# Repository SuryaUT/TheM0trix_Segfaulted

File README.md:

# 🕶️ The M0+rix: Segfaulted

A Matrix-themed multiplayer FPS built entirely on the MSPM0G3507 microcontroller. Featuring low-level graphics rendering via raycasting, joystick control, UART-based multiplayer, and a fully custom 3D-printed enclosure.

---

## Table of Contents

* [🎮 Game Description](#-game-description)
* [🔥 Features](#-features)
* [🚀 Getting Started](#-getting-started)
* [🔩 Parts List](#-parts-list)
* [🎮 Controls](#-controls)
* [🖼️ Screenshots / Demo](#️-screenshots--demo)
* [🛠️ Enclosure](#-enclosure)
* [👥 Authors](#-authors)

---

## 🎮 Game Description

Reality is a pointer… and you just dereferenced NULL.

Welcome to **The M0+rix: Segfaulted**, a handheld first-person shooter where the only way out is through the system’s deepest vulnerabilities. Running on the MSPM0 microcontroller, this game turns embedded systems into battlegrounds, with PVP combat over UART and a retro-style 3D world.

Dodge enemy fire, navigate the simulation, and exploit every loophole in the code—because in this world, even one bad instruction could bring everything crashing down. Are you the debugger or just another broken process?

---

## 🔥 Features:

* ✅ First-person shooter with a Matrix-inspired digital battlefield
* ✅ Real-time PVP over UART – battle your opponent in low-level style
* ✅ Optimized for MSPM0 – embedded gaming meets high-speed action
* ✅ Handheld experience – take the simulation anywhere
* ✅ Segfault or escape? – The system is unstable, and only one player will survive

💾 Flash in. Boot up. Overwrite reality.

---

## 🚀 Getting Started

1.  **Clone this repo**

    ```bash
    git clone https://github.com/SuryaUT/TheM0trix_Segfaulted.git
    ```

2.  **Import into Code Composer Studio** <br>
    Open CCS. Go to **File > Import > Code Composer Studio Projects**. Select the cloned folder. Make sure the target is set to **MSPM0G3507**. Click **Finish**.

3.  **Build and Flash** <br>
    Plug in the LaunchPad. Press the build button. Flash to the board.

---

## 🔩 Parts List

| Ref. | Value | Datasheet | Footprint | Qty |
| :--- | :--- | :--- | :--- | :--- |
| C1 | 1uF | ~ | ECE319K:CP\_Radial\_Tantal200mil | 1 |
| C2 | 4.7uF | ~ | ECE319K:CP\_Radial\_Tantal200mil | 1 |
| C3, C4 | 0.1uF | ~ | ECE319K:C\_Axial\_200mil | 2 |
| D1, D4 | LED | Link 1, Link 2 | ECE319K:LED\_D5.0mm | 2 |
| H1, H2, H3, H4 | – | ~ | ECE319K:MountingHole\_4\_40 | 4 |
| J1 | AudioJack | ~ | ECE319K:Jack\_3.5mm\_CUI\_SJ1-3523N\_Horizontal | 1 |
| J2 | Speaker | ~ | ECE319K:PinHeader\_1x02\_P2.54mm\_Vertical | 1 |
| J3 | UART1 | ~ | ECE319K:PinHeader\_1x03\_P2.54mm\_Vertical | 1 |
| J6 | GND | ~ | ECE319K:Testpoint\_1x02\_P2.54mm | 1 |
| J7 | DACOUT | ~ | ECE319K:Testpoint\_1x02\_P2.54mm | 1 |
| J8 | Joystick | SparkFun | ECE319K:SparkfunJoystick | 1 |
| JP1 | TExaS | ~ | ECE319K:PinHeader\_1x03\_P2.54mm\_Vertical | 1 |
| JP2, JP3, JP4 | Jumper\_3\_Open | ~ | ECE319K:PinHeader\_1x03\_P2.54mm\_Vertical | 3 |
| R1 | 470Ω | Resistors | ECE319K:R\_Axial\_DIN0204\_L3.6mm\_D1.6mm\_P7.62mm\_Horizontal | 1 |
| R4–R8 | 1.5kΩ | Resistors | ECE319K:R\_Axial\_DIN0204\_L3.6mm\_D1.6mm\_P7.62mm\_Horizontal | 5 |
| R9–R11 | 12kΩ | Resistors | ECE319K:R\_Axial\_DIN0204\_L3.6mm\_D1.6mm\_P7.62mm\_Horizontal | 3 |
| R12–R15, R17, R19 | 10kΩ | Resistors | ECE319K:R\_Axial\_DIN0204\_L3.6mm\_D1.6mm\_P7.62mm\_Horizontal | 6 |
| R16 | 20kΩ | Resistors | ECE319K:R\_Axial\_DIN0204\_L3.6mm\_D1.6mm\_P7.62mm\_Horizontal | 1 |
| R18 | 220Ω | Resistors | ECE319K:R\_Axial\_DIN0204\_L3.6mm\_D1.6mm\_P7.62mm\_Horizontal | 1 |
| SW1 | RELOAD | ~ | ECE319K:SW\_PUSH\_6mm | 1 |
| SW2 | LEFT | ~ | ECE319K:SW\_PUSH\_6mm | 1 |
| SW3 | SWAP | ~ | ECE319K:SW\_PUSH\_6mm | 1 |
| SW4 | RIGHT | ~ | ECE319K:SW\_PUSH\_6mm | 1 |
| SW5 | SHOOT | ~ | ECE319K:Side\_Switch | 1 |
| TP1 | 3.3V | ~ | ECE319K:Testpoint\_1x02\_P2.54mm | 1 |
| U2 | LP-MSPM0G3507 | TI Dev Board | ECE319K:ti\_LP\_MSPM0G3507 | 1 |
| U3 | MCP34119P | Datasheet | ECE319K:DIP-8\_W7.62mm\_LongPads | 1 |
| U4 | HiLetGo\_ST7735R | Display | ECE319K:hiletgo\_st7735r | 1 |
| U5 | ULN2003B | ULN2003B | ECE319K:DIP-16\_W7.62mm | 1 |
| U6 | TSOP31438 | TSOP31438 | ECE319K:TSOP31438 | 1 |
| ~ | SD Card | ~ | ~ | 1 |
| ~ | Wire Pack | ~ | ~ | 1 |

*Note: Side\_Switch was a custom footprint made by placing surface mount plates the width of switch legs on the front and back of the PCB, such that a switch could be soldered to face away from the side of the PCB, acting like a trigger.*

📦 Full schematic & PCB design files available in “M0+rixPCBFiles” folder

---

## 🎮 Controls

| Control | Action |
| :--- | :--- |
| Joystick | Move Forward, Backward, Strafe Left and Right |
| Trigger Button | Fire weapon |
| Left Button | Rotate Left |
| Right Button | Rotate Right |
| Top Button | Reload/Respawn |
| Bottom Button | Switch Item |

---

## 🖼️ Screenshots / Demo

Gameplay demo available on YouTube [here](https://www.youtube.com/watch?v=fk33UKtkELA).

---

## 🛠️ Enclosure

* Designed in Fusion 360
* Snap-fit top cover
* Gamepad-style ergonomic shell

---

## 👥 Authors

* Elijah Silguero
* Surya Balaji

Special thanks to Dr. Yerrabali, Dr. Valvano, and Dr. Tiwari at The University of Texas at Austin for their instruction and help with this project!

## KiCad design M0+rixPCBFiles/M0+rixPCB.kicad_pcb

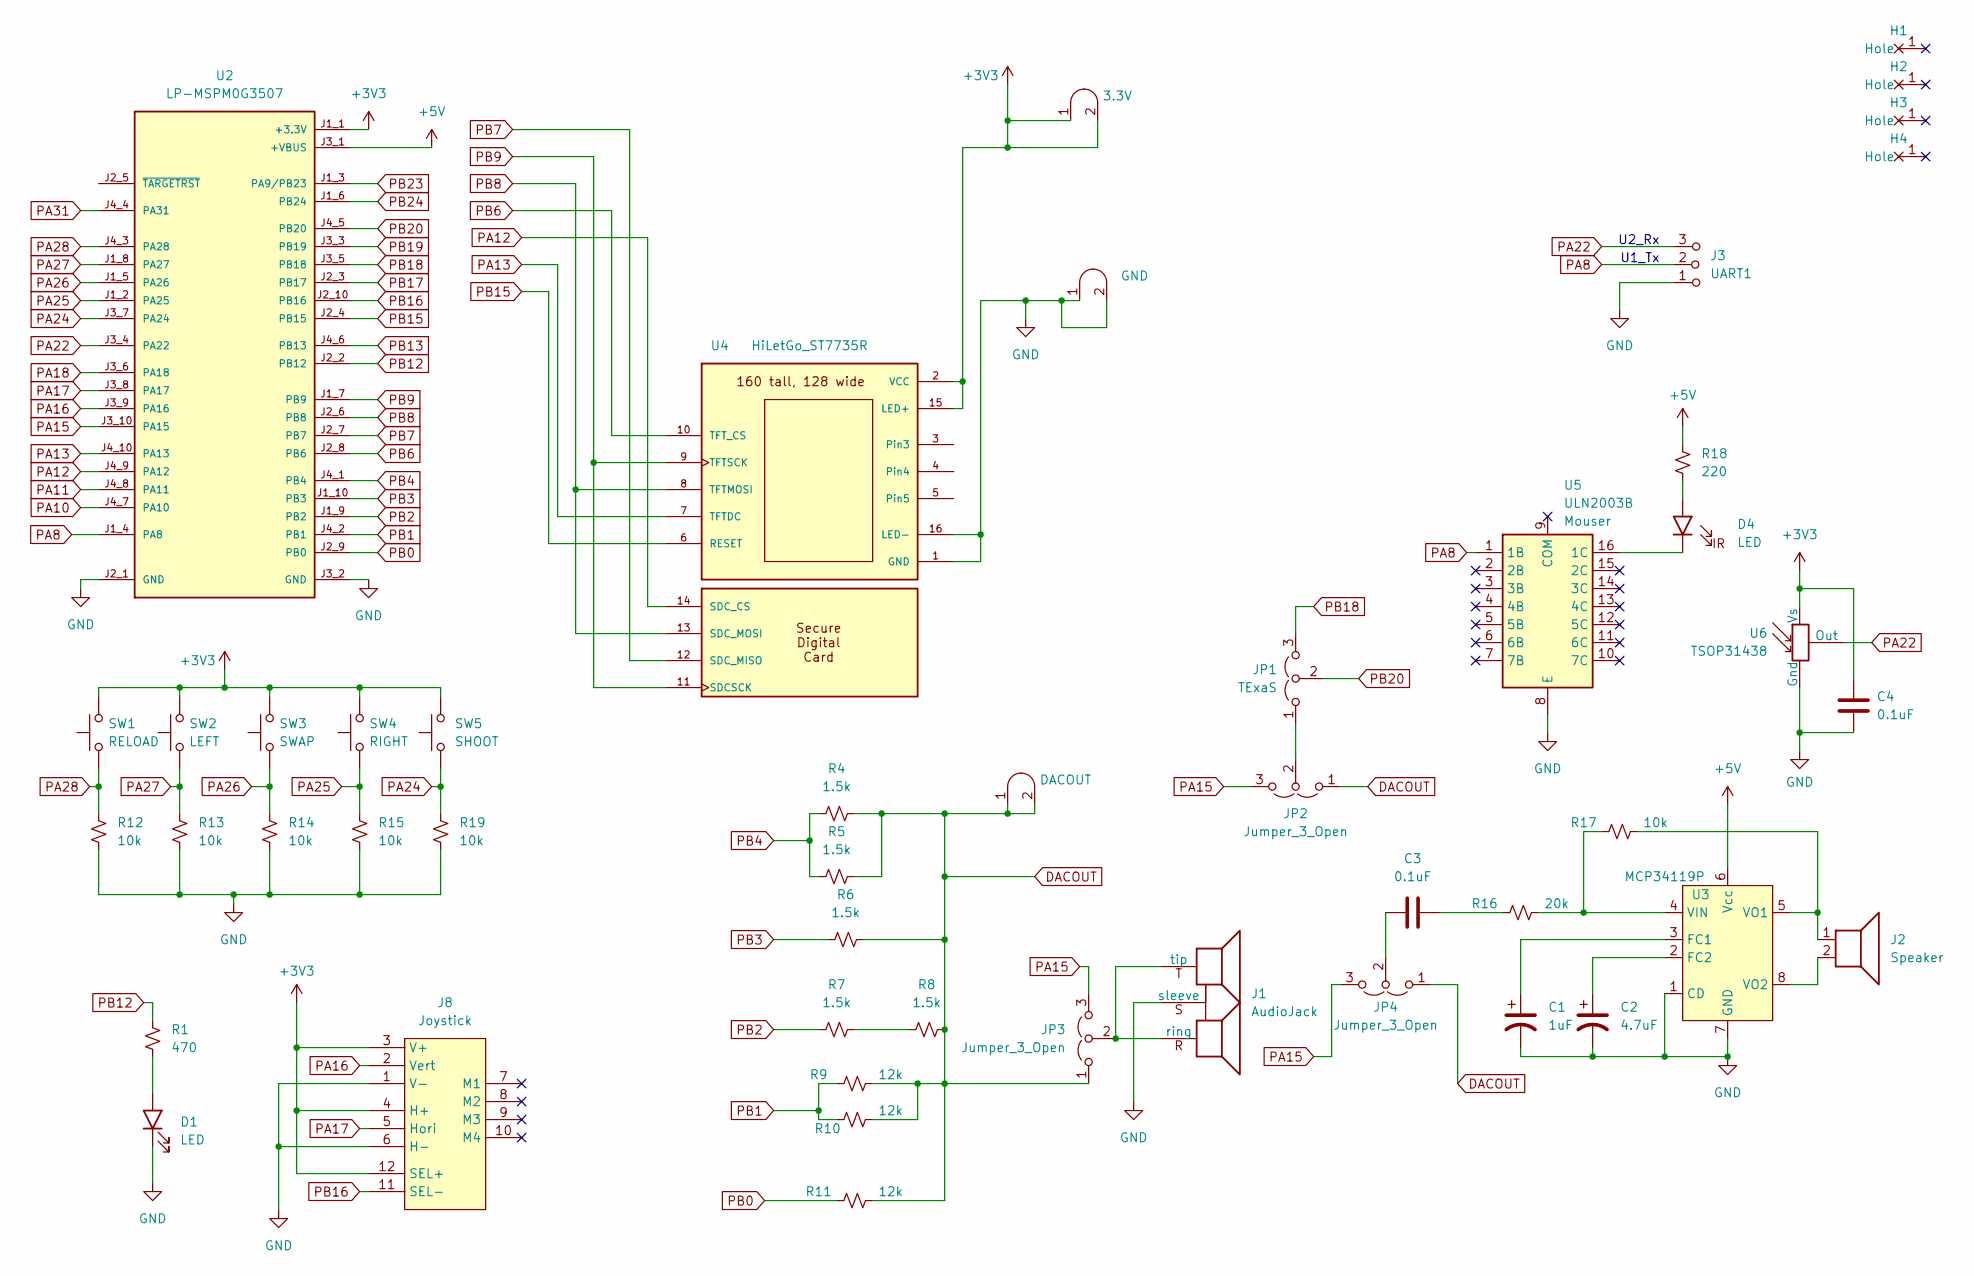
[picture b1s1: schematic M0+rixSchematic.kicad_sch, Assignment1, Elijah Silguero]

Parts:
C1: 1uF; CP_Radial_Tantal200mil
C2: 4.7uF; CP_Radial_Tantal200mil
C3, C4: 0.1uF; C_Axial_200mil
D1, D4: LED; LED_D5.0mm
H1, H2, H3, H4: MountingHole_4_40
J1: AudioJack; Jack_3.5mm_CUI_SJ1-3523N_Horizontal
J2: Speaker; PinHeader_1x02_P2.54mm_Vertical
J3: UART1; PinHeader_1x03_P2.54mm_Vertical
J6: GND; Testpoint_1x02_P2.54mm
J7: DACOUT; Testpoint_1x02_P2.54mm
J8: Joystick; SparkfunJoystick
JP1: TExaS; PinHeader_1x03_P2.54mm_Vertical
JP2, JP3, JP4: Jumper_3_Open; PinHeader_1x03_P2.54mm_Vertical
R1: 470; R_Axial_DIN0204_L3.6mm_D1.6mm_P7.62mm_Horizontal
R4, R5, R6, R7, R8: 1.5k; R_Axial_DIN0204_L3.6mm_D1.6mm_P7.62mm_Horizontal
R9, R10, R11: 12k; R_Axial_DIN0204_L3.6mm_D1.6mm_P7.62mm_Horizontal
R12, R13, R14, R15, R17, R19: 10k; R_Axial_DIN0204_L3.6mm_D1.6mm_P7.62mm_Horizontal
R16: 20k; R_Axial_DIN0204_L3.6mm_D1.6mm_P7.62mm_Horizontal
R18: 220; R_Axial_DIN0204_L3.6mm_D1.6mm_P7.62mm_Horizontal
SW1: RELOAD; SW_PUSH_6mm
SW2: LEFT; SW_PUSH_6mm
SW3: SWAP; SW_PUSH_6mm
SW4: RIGHT; SW_PUSH_6mm
SW5: SHOOT; Side_Switch
TP1: 3.3V; Testpoint_1x02_P2.54mm
U2: LP-MSPM0G3507; ti_LP_MSPM0G3507
U3: MCP34119P; DIP-8_W7.62mm_LongPads
U4: HiLetGo_ST7735R; hiletgo_st7735r
U5: ULN2003B; DIP-16_W7.62mm
U6: TSOP31438

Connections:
+3V3: C4.1, J8.3 (V+), J8.4 (H+), J8.12 (SEL+), SW1.2, SW2.2, SW3.2, SW4.2, SW5.2, TP1.1 (A), TP1.2 (B), U2.J1_1 (+3.3V), U4.2 (VCC), U4.15 (LED+), U6.2 (Vs)
+5V: R18.1, U2.J3_1 (+VBUS), U3.6 (Vcc)
DACOUT: J7.1 (A), J7.2 (B), JP2.1 (A), JP3.1 (A), JP4.1 (A), R4.1, R5.1, R6.1, R8.1, R9.1, R10.1, R11.1
GND: C1.2, C2.2, C4.2, D1.1 (K), J1.S (sleeve), J3.1 (A), J6.1 (A), J6.2 (B), J8.1 (V-), J8.6 (H-), R12.2, R13.2, R14.2, R15.2, R19.2, U2.J2_1 (GND), U2.J3_2 (GND), U3.1 (CD), U3.7 (GND), U4.1 (GND), U4.16 (LED-), U5.8 (E), U6.1 (Gnd)
unnamed: C3.2, R16.2
unnamed: D1.2 (A), R1.2
unnamed: D4.2 (A), R18.2
unnamed: D4.1 (K), U5.16 (1C)
unnamed: J1.R (ring), J1.T (tip), JP3.2 (C)
unnamed: JP1.1 (A), JP2.2 (C)
unnamed: C3.1, JP4.2 (C)
unnamed: R7.1, R8.2
unnamed: C1.1, U3.3 (FC1)
unnamed: C2.1, U3.2 (FC2)
unnamed: R16.1, R17.2, U3.4 (VIN)
unnamed: J2.1, R17.1, U3.5 (VO1)
unnamed: J2.2, U3.8 (VO2)
PA8: J3.2 (B), U2.J1_4 (PA8), U5.1 (1B)
PA10: U2.J4_7 (PA10)
PA11: U2.J4_8 (PA11)
PA12: U2.J4_9 (PA12), U4.14 (SDC_CS)
PA13: U2.J4_10 (PA13), U4.7 (TFTDC)
PA15: JP2.3 (B), JP3.3 (B), JP4.3 (B), U2.J3_10 (PA15)
PA16: J8.2 (Vert), U2.J3_9 (PA16)
PA17: J8.5 (Hori), U2.J3_8 (PA17)
PA18: U2.J3_6 (PA18)
PA22: J3.3 (C), U2.J3_4 (PA22), U6.3 (Out)
PA24: R19.1, SW5.1, U2.J3_7 (PA24)
PA25: R15.1, SW4.1, U2.J1_2 (PA25)
PA26: R14.1, SW3.1, U2.J1_5 (PA26)
PA27: R13.1, SW2.1, U2.J1_8 (PA27)
PA28: R12.1, SW1.1, U2.J4_3 (PA28)
PA31: U2.J4_4 (PA31)
PB0: R11.2, U2.J2_9 (PB0)
PB1: R9.2, R10.2, U2.J4_2 (PB1)
PB2: R7.2, U2.J1_9 (PB2)
PB3: R6.2, U2.J1_10 (PB3)
PB4: R4.2, R5.2, U2.J4_1 (PB4)
PB6: U2.J2_8 (PB6), U4.10 (TFT_CS)
PB7: U2.J2_7 (PB7), U4.12 (SDC_MISO)
PB8: U2.J2_6 (PB8), U4.8 (TFTMOSI), U4.13 (SDC_MOSI)
PB9: U2.J1_7 (PB9), U4.9 (TFTSCK), U4.11 (SDCSCK)
PB12: R1.1, U2.J2_2 (PB12)
PB13: U2.J4_6 (PB13)
PB15: U2.J2_4 (PB15), U4.6 (RESET)
PB16: J8.11 (SEL-), U2.J2_10 (PB16)
PB17: U2.J2_3 (PB17)
PB18: JP1.3 (B), U2.J3_5 (PB18)
PB19: U2.J3_3 (PB19)
PB20: JP1.2 (C), U2.J4_5 (PB20)
PB23: U2.J1_3 (PA9/PB23)
PB24: U2.J1_6 (PB24)

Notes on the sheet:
U2_Rx
U1_Tx

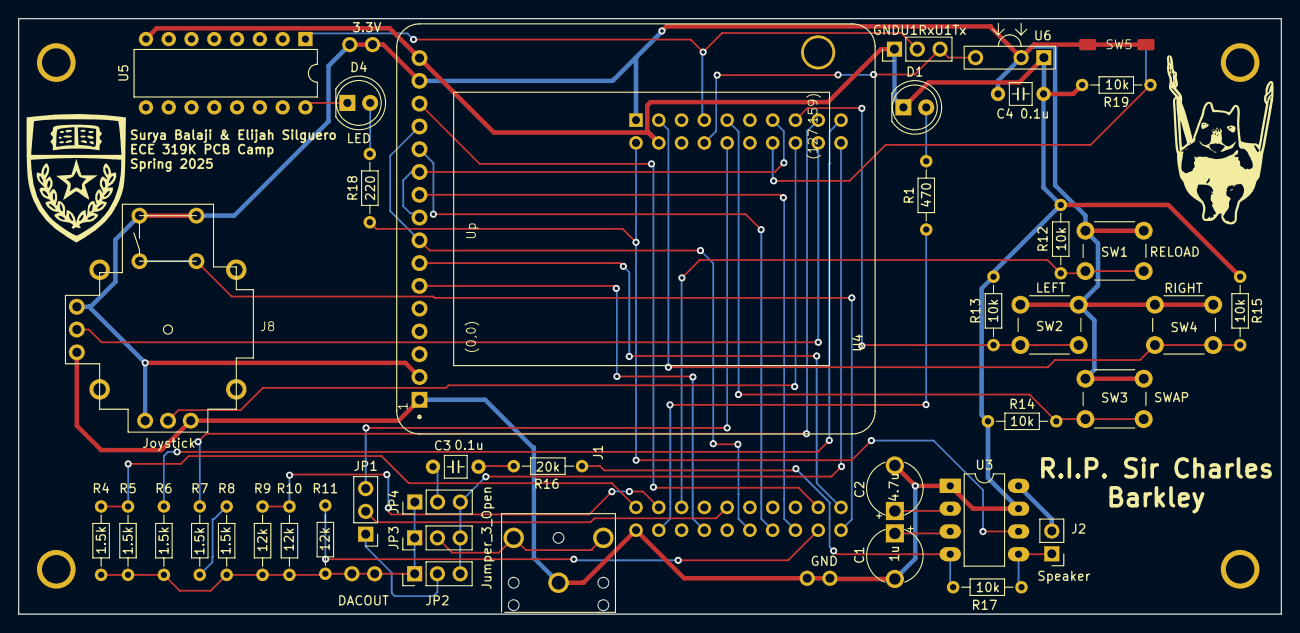
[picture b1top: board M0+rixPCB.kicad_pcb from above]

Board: 2 copper layers, 140.8 x 66.4 mm, 48 parts (1 on the bottom side), 43 nets.

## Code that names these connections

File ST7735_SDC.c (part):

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// **********ST7735 TFT and SDC*******************
// ST7735
// Backlight (pin 10)     to +3.3 V
// MISO (pin 9)           to SPI1 POCI: PB7
// SCK (pin 8)            to SPI1 SCLK: PB9
// MOSI (pin 7)           to SPI1 PICO: PB8
// TFT_CS (pin 6)         to GPIO:  PB6
// CARD_CS (pin 5)        to PA12 (GPIO)
// Data/Command (pin 4)   to PA13 (GPIO), high for data, low for command
// RESET (pin 3)          to PB15 (GPIO)
// VCC (pin 2)            to +3.3 V
// Gnd (pin 1)            to ground

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// ST7735
// LED-   (pin 16) TFT, to ground
// LED+   (pin 15) TFT, to +3.3 V
// SD_CS  (pin 14) SDC, to PA12 chip select
// MOSI   (pin 13) SDC, to PB8 MOSI
// MISO   (pin 12) SDC, to PB7 MISO
// SCK    (pin 11) SDC, to serial clock
// CS     (pin 10) TFT, to PB6  GPIO
// SCL    (pin 9)  TFT, to PB9  SPI1 SCLK
// SDA    (pin 8)  TFT, to PB8  MOSI SPI1 PICO
// A0     (pin 7)  TFT, to PA13 Data/Command, high for data, low for command
// RESET  (pin 6)  TFT, to PB15 reset (GPIO), low to reset
// NC     (pins 3,4,5)
// VCC    (pin 2)       to +3.3 V
// GND    (pin 1)       to ground
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#include <stdio.h>
#include <stdlib.h>
#define SDC_CS_PA12 1
#define TFT_CS_LOW()     (GPIOB->DOUTCLR31_0 = (1<<6))   // PB6 low
#define TFT_CS_HIGH()    (GPIOB->DOUTSET31_0 = (1<<6))   // PB6 high

// PA12 output used for SDC CS
#if SDC_CS_PA12
#define SDC_CS           GPIOA
#define SDC_CS_PIN       (1<<12)         // CS controlled by software
#define SDC_CS_LOW()     (SDC_CS->DOUTCLR31_0 = SDC_CS_PIN)   // PA12 low
#define SDC_CS_HIGH()    (SDC_CS->DOUTSET31_0 = SDC_CS_PIN)   // PA12 high
#endif
// disk_initialize will initialize SPI1 for both TFT and SDC
// 16 rows (0 to 15) and 21 characters (0 to 20)
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void TFT_OutData(char data){char response;
 // while((SPI1->STAT&0x02) == 0x00){}; // spin if TxFifo full
  while((SPI1->STAT&0x10) == 0x10){}; // spin if SPI busy
  SDC_CS_HIGH(); // PA12 high
  TFT_CS_LOW();  // PB6 low
  GPIOA->DOUTSET31_0 = 1<<13;         // RS=PA13=1 for data
  SPI1->TXDATA = data;
  while((SPI1->STAT&0x04) == 0x04){}; // spin SPI RxFifo empty
  response = SPI1->RXDATA; // has no meaning, flush
  TFT_CS_HIGH();  // PB6 high
}
 //---------TFT_OutCommand------------
 // Output 8-bit command to SPI port
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 // Output: none
 void TFT_OutCommand(char command){char response;
   while((SPI1->STAT&0x10) == 0x10){}; // spin if SPI busy
   SDC_CS_HIGH(); // PA12 high
   TFT_CS_LOW();  // PB6 low
   GPIOA->DOUTCLR31_0 = 1<<13;         // RS=PA13=0 for command
   SPI1->TXDATA = command;
   while((SPI1->STAT&0x10) == 0x10){}; // spin if SPI busy
   response = SPI1->RXDATA; // has no meaning, flush
   TFT_CS_HIGH();  // PB6 high
 }
// Companion code to the above tables.  Reads and issues
// a series of LCD commands stored in ROM byte array.
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
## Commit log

2025-03-27 Implimented Textured Walls
    Next Steps: merge with buffer to eliminate smearing and work on bitmap conversion to create detailed custom textures
2025-03-27 Implimented .bmp to texture conversion
    made .py script to convert .bmp files to c arrays for usable textures
2025-03-27 Updared Textures.c for .bmp use
    Tested .bmp converted c arrays in textures with 8 tests (8th successful!!!)
2025-03-27 Added another .bmp texture and updated converter
    made texture 7 a different circuit board texture and updated converter to create const instead of static const arrays
2025-03-27 Generalized converter & added Sir Charles Barkley
    Sir Charles Barkley is in the game as a texture (will be easter egg), and converter has titles of arrays generalized to "myTexture"
2025-03-27 Added more textures and defined texture indicies
    Added two matrix textures to textures.c, defined indices with names for clarity, and cleaned extraneous comments on graphics.c for readability
2025-03-27 Adjusted printed c array format
2025-03-27 Texture index definitions in textures.h
2025-03-27 Implemented textures with buffer
2025-03-28 Updated resolution of textures to 64 x 64
    Rewrote bitmap to C converter Python script for 64 x 64 bitmap conversion, changed definitions in both bitmap to C converter Python script and textures.h to 64 x 64
2025-03-28 Create test
2025-03-28 Uploaded texture bmps and pngs
2025-03-28 Converter takes folder & writes to .txt file
    bmp to C array converter takes folder with both/either png and/or bmp files and writes output to .txt file for easy copying; added new arrays to textures.h; TexArrays.txt is text file to write C arra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
2025-03-28 Added comments of directory to simplify use
2025-03-29 Sprites
2025-03-29 Full upload
2025-03-29 add .gitignore
2025-03-29 Update project name
2025-03-29 test
2025-03-29 Added Foreground Sprites
2025-03-31 Reorganized input functions
2025-03-31 Added new sounds and ammo logic
2025-03-31 began inventory implementation/graphics
2025-04-01 Progress on inventory implementation
2025-04-01 Added shotgun to items
2025-04-02 Added sprint ability from joystick button
2025-04-02 Dynamic ammo for different weapons
2025-04-03 Added gun flash, expiring items, dynamic crosshair
2025-04-03 Added ammo pickup
2025-04-04 Fixed inventory game logic bugs
2025-04-04 Fixed ammo game logic bugs
2025-04-04 Prepare for 2-player by adding otherHealth
2025-04-05 Added sound for realoading with no ammo
2025-04-05 Begin UART
2025-04-05 Fixed muzzle position bug
2025-04-06 UART char transmission
2025-04-06 Implimented cross controller UART position updates
2025-04-07 Synchronized player positions to move enemy sprite
2025-04-07 added interrupt for uart transmission
2025-04-07 more uart debugging
2025-04-07 Removed end sentinel check for increased speed
2025-04-07 working health deduction from weapons
2025-04-07 add respawn
2025-04-07 health sync
2025-04-07 more uart
2025-04-07 fix uart bugs
2025-04-08 Updated agent sprite and reset UART functionality
2025-04-08 Refactored UART Reception, fixed other player flicker
2025-04-09 UART fixed with position and health sync
2025-04-09 Reorganized synchronization functions, fixed medkit glitch
2025-04-09 Begin item sync (pickup and spawn(
2025-04-09 Got item pickup sync working
2025-04-09 Begin item respawn
2025-04-09 Implimented 30 sec item respawn with TIMG6
2025-04-10 Added Agent Images/Sprites
2025-04-10 Uploaded Diff Agent PNGs
2025-04-10 Synchronize player directions, for more immersive experience
2025-04-11 Added rifle w/rapidfire (needs ground sprite and UART testing) and slowed rotate speed
2025-04-11 Fixed Pistol Item Bug
2025-04-14 Unified sprite formats, updated weapon sprites/images, lengthened respawn time
2025-04-15 Truly random placement of items, communicated from dominant controller to the other
2025-04-15 Added more items
2025-04-15 New Pistol Image
2025-04-15 Implement item replacement
2025-04-15 Added temporary invulnerability on respawn
2025-04-16 Added leaderboard and centered spawn
2025-04-16 Fixed flash positions
2025-04-16 Bug fixes
2025-04-18 A bunch of changes, bug fixes, added profs, etc.
2025-04-18 Fixex Empty Inventory Ammo Bug
2025-04-18 Fixed Empty Invent Pointer Issue
2025-04-21 SDC-Compatibility
2025-04-21 Added images from SDC
2025-04-22 Add images
2025-04-22 Merged CODE and MENU to create LDSC (Loading Screen)
2025-04-22 Add direction of hit; begin sound streaming from SDC
2025-04-22 SD card sound
2025-04-24 Add menu screens
2025-04-24 Multiple language support
2025-04-24 Added Railgun & Fixed Sprite Spawn Bug
2025-04-24 Begin menu sync
2025-04-24 continue menu sync
2025-04-24 interrupt based menu sync
2025-04-24 Menu sync successful
2025-04-24 menu sync complete
2025-04-24 sync restart test
2025-04-24 fix restart menu bug
2025-04-24 Increase respawn time
2025-04-24 Fix dialogue skip
2025-04-24 Change dominant dialogue screen
2025-04-25 fix shotgun damage discrepancy
2025-04-25 increase item respawn time
2025-04-26 Disable gun when dead
2025-04-27 ammo turn red when mag is empty
2025-04-27 Sync on bootup
2025-04-27 Dialogue Screen sync
2025-04-27 update images
2025-04-28 Add pibb image
2025-04-28 proper handshake
2025-04-28 add sounds
2025-04-28 Added New Speech Audios
2025-04-28 Fix dialogue sync
2025-04-28 Fix menu return bug
2025-04-28 Fix crosshairs
2025-04-28 added pibble studios screen
2025-04-28 Fix language menu options
2025-04-28 Update respawn screens
2025-04-28 Add weapon range
2025-04-28 update dialogue sounds
2025-04-28 keep music playing at end of dialogue until handshake completes
2025-04-28 fix sound bug at end of dialogue
2025-04-28 update map2
2025-04-28 test map2
2025-04-28 finish map2
2025-04-29 reaorganize player state
2025-04-29 minor bug fixes
2025-04-29 reduce sprint speed
2025-05-30 Added PCB Files

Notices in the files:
ST7735_SDC.c:
MIT license, all text above must be included in any redistribution
Copyright 2024 by Jonathan W. Valvano, valvano@mail.utexas.edu
